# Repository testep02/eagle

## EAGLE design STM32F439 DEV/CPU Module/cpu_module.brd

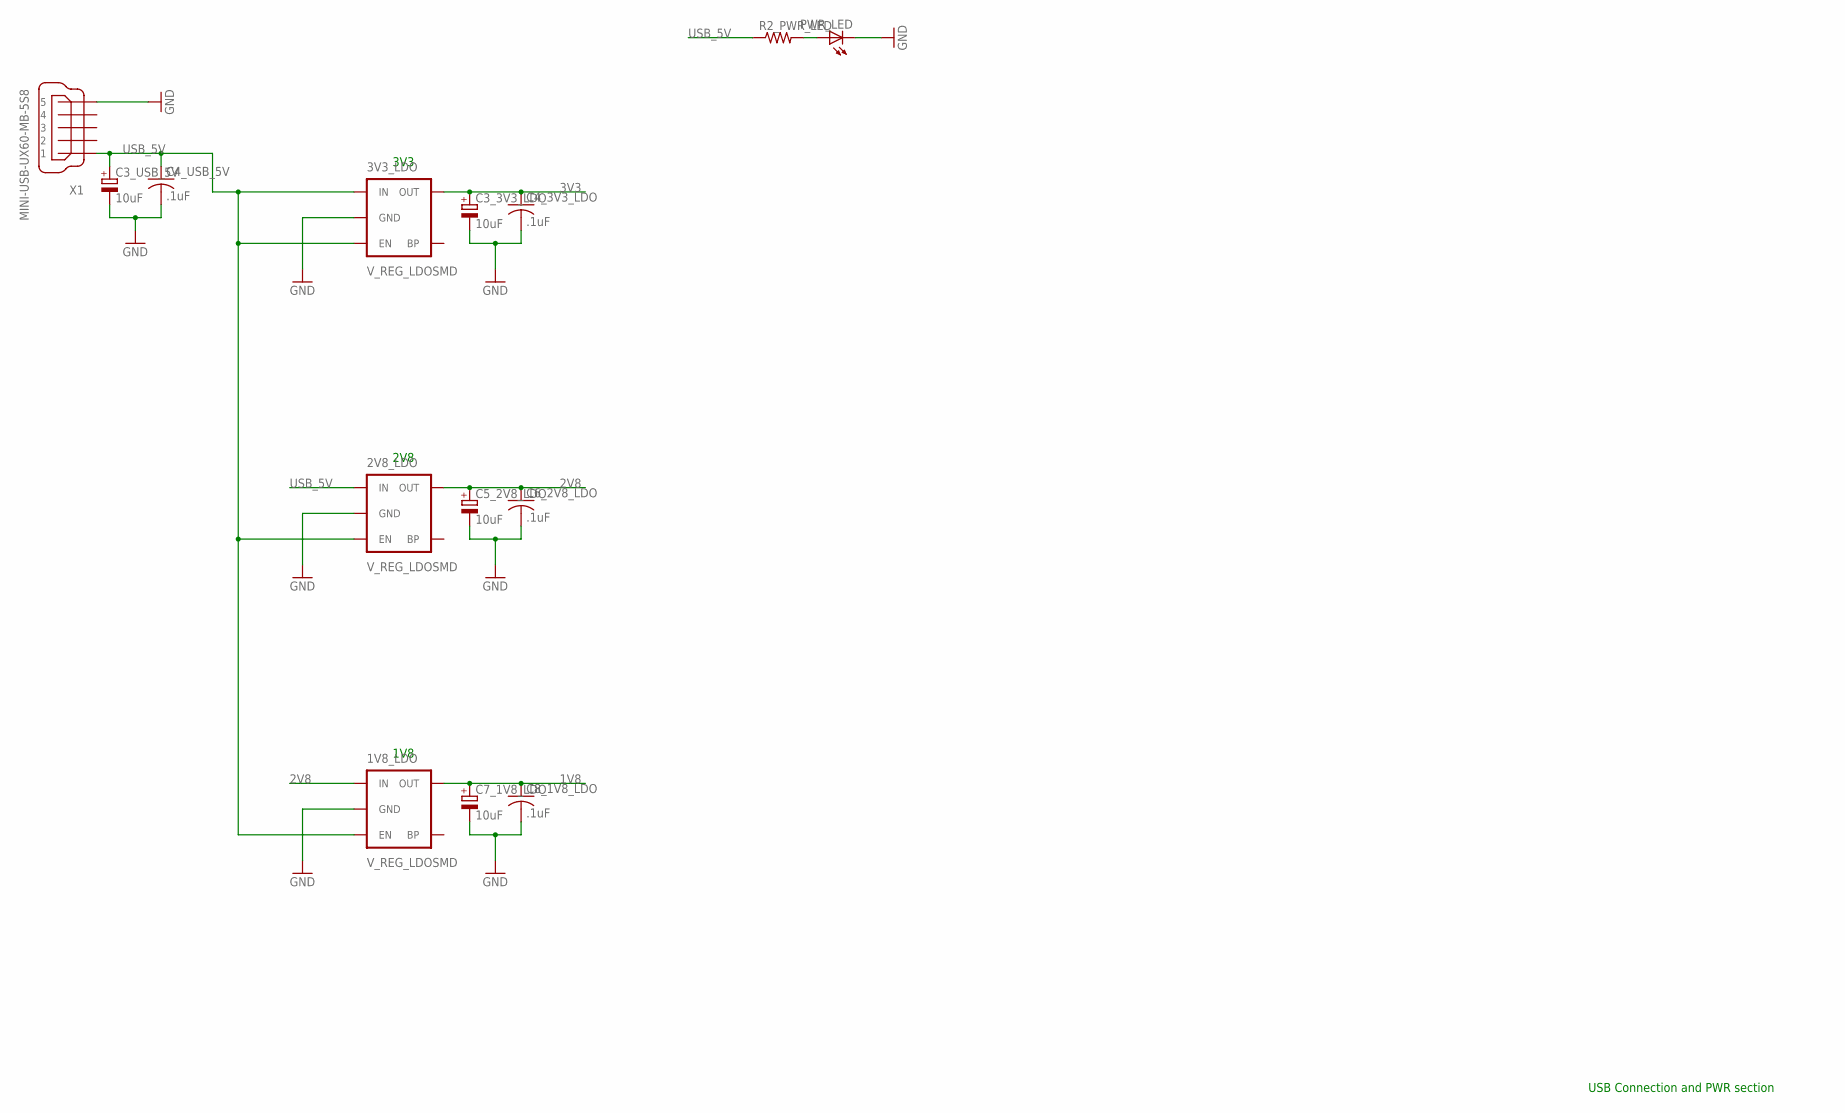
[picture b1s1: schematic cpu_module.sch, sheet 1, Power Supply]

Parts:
1V8_LDO, 2V8_LDO, 3V3_LDO: V_REG_LDOSMD; SOT23-5
C3_3V3_LDO, C3_USB_5V, C5_2V8_LDO, C7_1V8_LDO: 10uF; SMC_A
C4_3V3_LDO, C4_USB_5V, C6_2V8_LDO, C8_1V8_LDO: .1uF; C0402
PWR_LED: LEDCHIP-LED0603; CHIP-LED0603
R2_PWR_LED: RESISTOR0402-RES; 0402-RES
X1: MINI-USB-UX60-MB-5S8; UX60-MB-5S8

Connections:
1V8: 1V8_LDO.5 (OUT), C7_1V8_LDO.+, C8_1V8_LDO.1; also elsewhere on the board
2V8: 1V8_LDO.1 (IN), 2V8_LDO.5 (OUT), C5_2V8_LDO.+, C6_2V8_LDO.1; also elsewhere on the board
3V3: 3V3_LDO.5 (OUT), C3_3V3_LDO.+, C4_3V3_LDO.1; also elsewhere on the board
GND: 1V8_LDO.2 (GND), 2V8_LDO.2 (GND), 3V3_LDO.2 (GND), C3_3V3_LDO.-, C3_USB_5V.-, C4_3V3_LDO.2, C4_USB_5V.2, C5_2V8_LDO.-, C6_2V8_LDO.2, C7_1V8_LDO.-, C8_1V8_LDO.2, PWR_LED.C, X1.5; also elsewhere on the board
unnamed: PWR_LED.A, R2_PWR_LED.2
USB_5V: 1V8_LDO.3 (EN), 2V8_LDO.1 (IN), 2V8_LDO.3 (EN), 3V3_LDO.1 (IN), 3V3_LDO.3 (EN), C3_USB_5V.+, C4_USB_5V.1, R2_PWR_LED.1, X1.1; also elsewhere on the board

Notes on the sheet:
USB Connection and PWR section
3V3
2V8
1V8

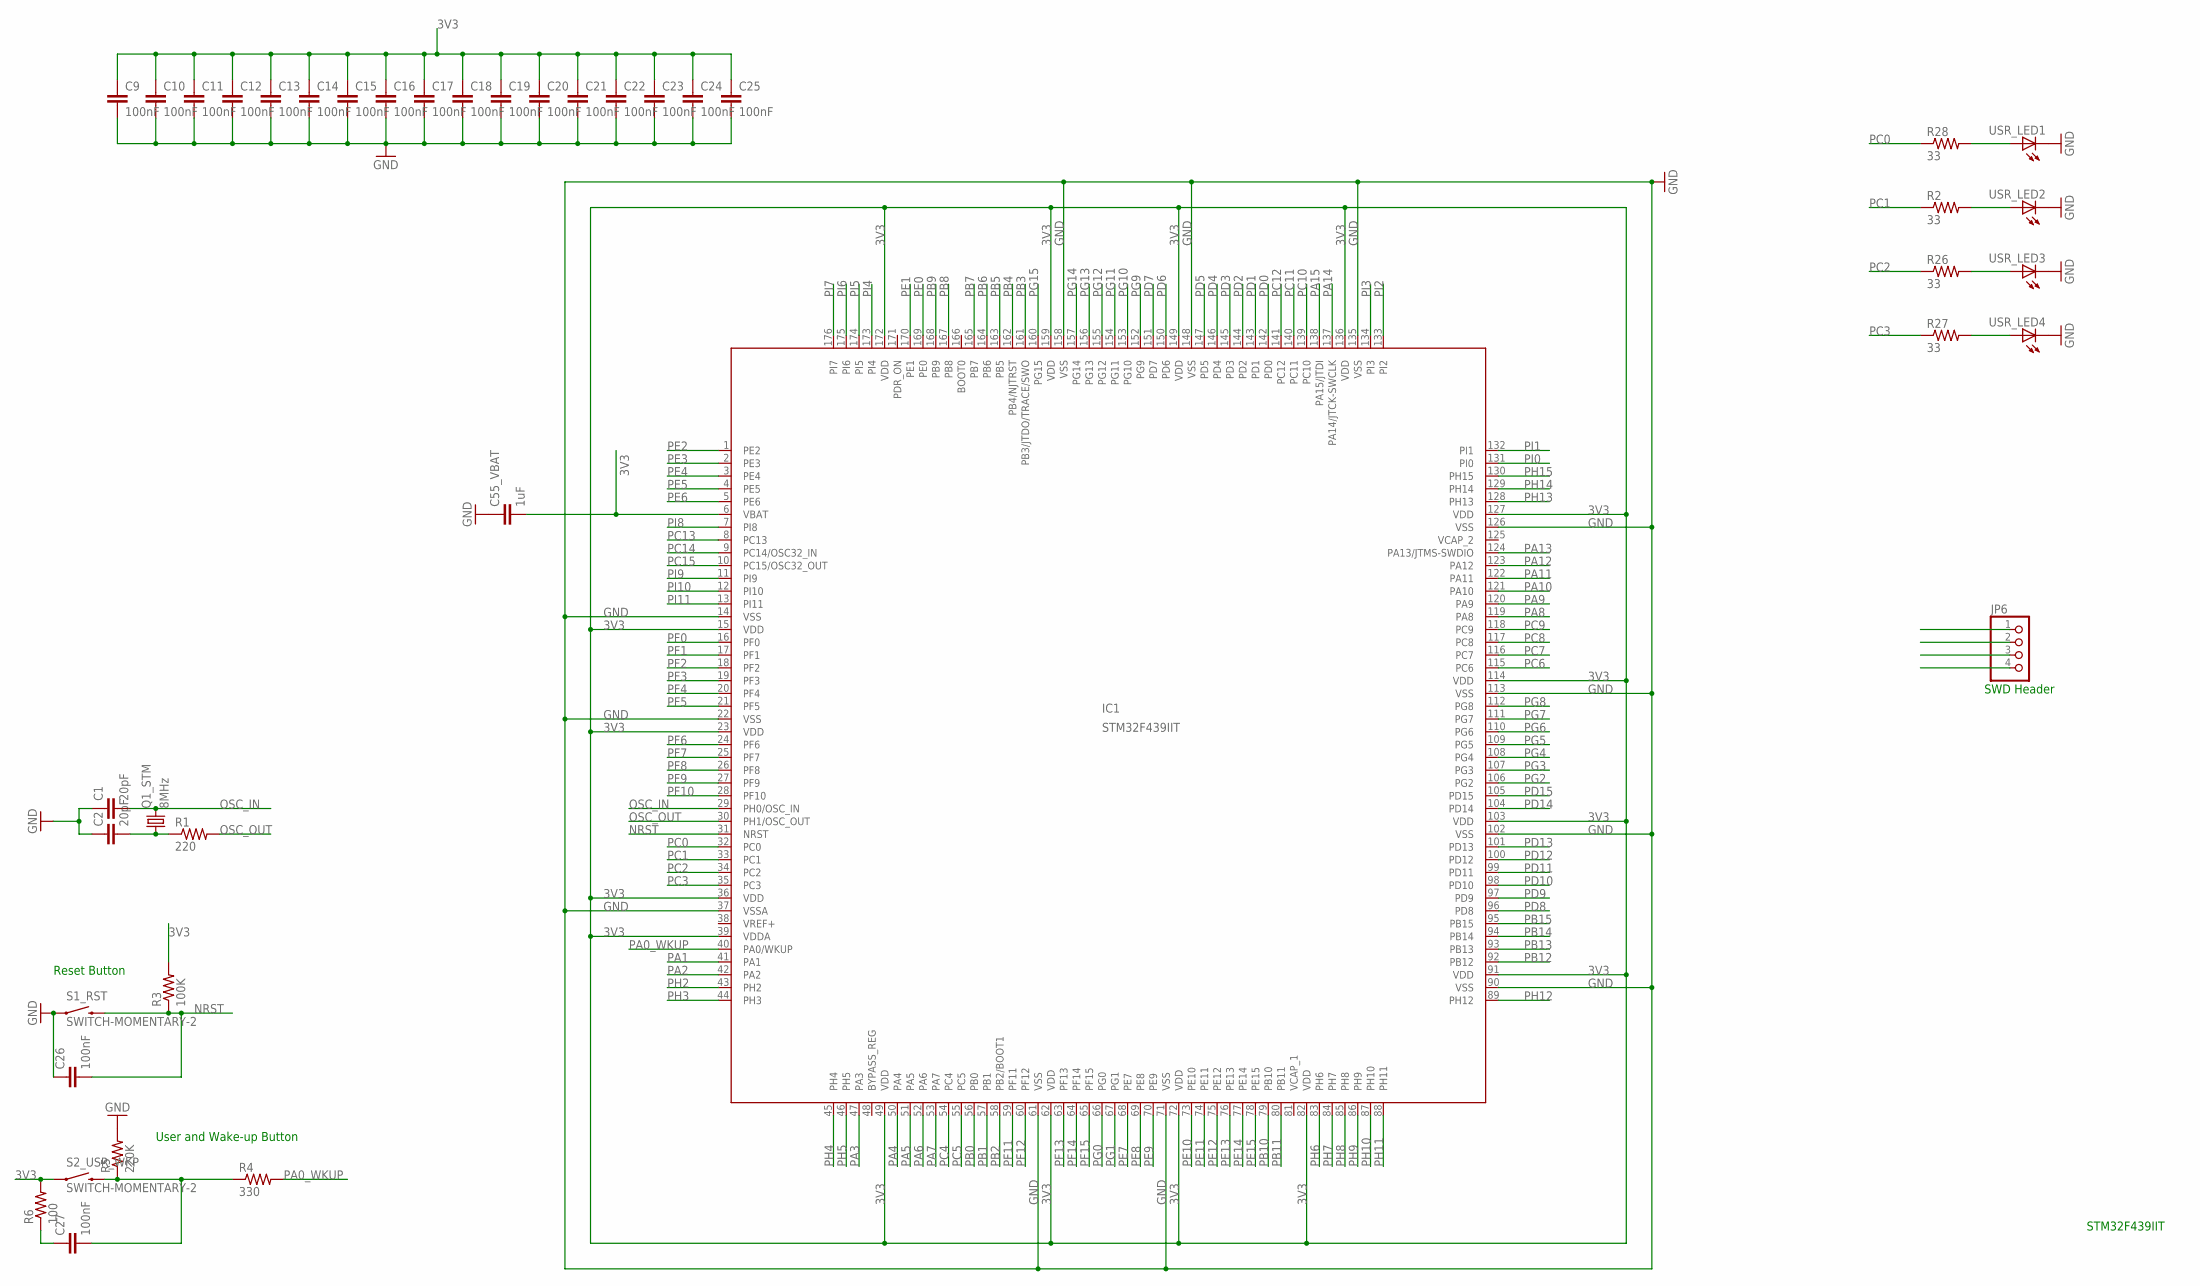
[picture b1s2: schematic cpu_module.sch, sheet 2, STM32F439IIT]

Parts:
C1, C2: 20pF; C0402
C9, C10, C11, C12, C13, C14, C15, C16, C17, C18, C19, C20, C21, C22, C23, C24, C25, C26, C27: 100nF; C0402
C55_VBAT: 1uF; C0402
IC1: STM32F439IIT; LQFP-176
JP6: PINHD-1X4/90; 1X04/90
Q1_STM: 8MHz; CTS406
R1: 220; 0402-RES
R2, R26, R27, R28: 33; 0402-RES
R3: 100K; 0402-RES
R4: 330; 0402-RES
R5: 220K; 0402-RES
R6: 100; 0402-RES
S1_RST, S2_USR_WKP: SWITCH-MOMENTARY-2; TACTILE_SWITCH_TALL
USR_LED1, USR_LED2, USR_LED3, USR_LED4: LEDCHIPLED_0805; CHIPLED_0805

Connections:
3V3: C9.1, C10.1, C11.1, C12.1, C13.1, C14.1, C15.1, C16.1, C17.1, C18.1, C19.1, C20.1, C21.1, C22.1, C23.1, C24.1, C25.1, C55_VBAT.2, IC1.6 (VBAT), IC1.15 (VDD), IC1.23 (VDD), IC1.36 (VDD), IC1.39 (VDDA), IC1.49 (VDD), IC1.62 (VDD), IC1.72 (VDD), IC1.82 (VDD), IC1.91 (VDD), IC1.103 (VDD), IC1.114 (VDD), IC1.127 (VDD), IC1.136 (VDD), IC1.149 (VDD), IC1.159 (VDD), IC1.172 (VDD), R3.2, R6.2, S2_USR_WKP.A2 (1); also elsewhere on the board
GND: C1.1, C2.1, C9.2, C10.2, C11.2, C12.2, C13.2, C14.2, C15.2, C16.2, C17.2, C18.2, C19.2, C20.2, C21.2, C22.2, C23.2, C24.2, C25.2, C26.1, C55_VBAT.1, IC1.14 (VSS), IC1.22 (VSS), IC1.37 (VSSA), IC1.61 (VSS), IC1.71 (VSS), IC1.90 (VSS), IC1.102 (VSS), IC1.113 (VSS), IC1.126 (VSS), IC1.135 (VSS), IC1.148 (VSS), IC1.158 (VSS), R5.2, S1_RST.A2 (1), USR_LED1.C, USR_LED2.C, USR_LED3.C, USR_LED4.C; also elsewhere on the board
unnamed: C2.2, Q1_STM.1, R1.1
unnamed: C27.2, R4.1, R5.1, S2_USR_WKP.B2 (2)
unnamed: C27.1, R6.1
unnamed: R28.2, USR_LED1.A
unnamed: R2.2, USR_LED2.A
unnamed: R26.2, USR_LED3.A
unnamed: R27.2, USR_LED4.A
NRST: C26.2, IC1.31 (NRST), R3.1, S1_RST.B2 (2); also elsewhere on the board
OSC_IN: C1.2, IC1.29 (PH0/OSC_IN), Q1_STM.3 (2)
OSC_OUT: IC1.30 (PH1/OSC_OUT), R1.2
PA0_WKUP: IC1.40 (PA0/WKUP), R4.2
PA1: IC1.41 (PA1); also elsewhere on the board
PA2: IC1.42 (PA2); also elsewhere on the board
PA3: IC1.47 (PA3); also elsewhere on the board
PA4: IC1.50 (PA4); also elsewhere on the board
PA5: IC1.51 (PA5); also elsewhere on the board
PA6: IC1.52 (PA6); also elsewhere on the board
PA7: IC1.53 (PA7); also elsewhere on the board
PA8: IC1.119 (PA8); also elsewhere on the board
PA9: IC1.120 (PA9); also elsewhere on the board
PA10: IC1.121 (PA10); also elsewhere on the board
PA11: IC1.122 (PA11); also elsewhere on the board
PA12: IC1.123 (PA12); also elsewhere on the board
PA13: IC1.124 (PA13/JTMS-SWDIO); also elsewhere on the board
PA14: IC1.137 (PA14/JTCK-SWCLK); also elsewhere on the board
PA15: IC1.138 (PA15/JTDI); also elsewhere on the board
PB0: IC1.56 (PB0); also elsewhere on the board
PB1: IC1.57 (PB1); also elsewhere on the board
PB2: IC1.58 (PB2/BOOT1); also elsewhere on the board
PB3: IC1.161 (PB3/JTDO/TRACE/SWO); also elsewhere on the board
PB4: IC1.162 (PB4/NJTRST); also elsewhere on the board
PB5: IC1.163 (PB5); also elsewhere on the board
PB6: IC1.164 (PB6); also elsewhere on the board
PB7: IC1.165 (PB7); also elsewhere on the board
PB8: IC1.167 (PB8); also elsewhere on the board
PB9: IC1.168 (PB9); also elsewhere on the board
PB10: IC1.79 (PB10); also elsewhere on the board
PB11: IC1.80 (PB11); also elsewhere on the board
PB12: IC1.92 (PB12); also elsewhere on the board
PB13: IC1.93 (PB13); also elsewhere on the board
PB14: IC1.94 (PB14); also elsewhere on the board
PB15: IC1.95 (PB15); also elsewhere on the board
PC0: IC1.32 (PC0), R28.1; also elsewhere on the board
PC1: IC1.33 (PC1), R2.1; also elsewhere on the board
PC2: IC1.34 (PC2), R26.1; also elsewhere on the board
PC3: IC1.35 (PC3), R27.1; also elsewhere on the board
PC4: IC1.54 (PC4); also elsewhere on the board
PC5: IC1.55 (PC5); also elsewhere on the board
PC6: IC1.115 (PC6); also elsewhere on the board
PC7: IC1.116 (PC7); also elsewhere on the board
PC8: IC1.117 (PC8); also elsewhere on the board
PC9: IC1.118 (PC9); also elsewhere on the board
PC10: IC1.139 (PC10); also elsewhere on the board
PC11: IC1.140 (PC11); also elsewhere on the board
PC12: IC1.141 (PC12); also elsewhere on the board
PC13: IC1.8 (PC13); also elsewhere on the board
PC14: IC1.9 (PC14/OSC32_IN); also elsewhere on the board
PC15: IC1.10 (PC15/OSC32_OUT); also elsewhere on the board
PD0: IC1.142 (PD0); also elsewhere on the board
PD1: IC1.143 (PD1); also elsewhere on the board
PD2: IC1.144 (PD2); also elsewhere on the board
PD3: IC1.145 (PD3); also elsewhere on the board
PD4: IC1.146 (PD4); also elsewhere on the board
PD5: IC1.147 (PD5); also elsewhere on the board
PD6: IC1.150 (PD6); also elsewhere on the board
PD7: IC1.151 (PD7); also elsewhere on the board
PD8: IC1.96 (PD8); also elsewhere on the board
PD9: IC1.97 (PD9); also elsewhere on the board
PD10: IC1.98 (PD10); also elsewhere on the board
PD11: IC1.99 (PD11); also elsewhere on the board
PD12: IC1.100 (PD12); also elsewhere on the board
PD13: IC1.101 (PD13); also elsewhere on the board
PD14: IC1.104 (PD14); also elsewhere on the board
PD15: IC1.105 (PD15); also elsewhere on the board
PDR_ON: IC1.171 (PDR_ON)
PE0: IC1.169 (PE0); also elsewhere on the board
PE1: IC1.170 (PE1); also elsewhere on the board
PE2: IC1.1 (PE2); also elsewhere on the board
PE3: IC1.2 (PE3); also elsewhere on the board
PE4: IC1.3 (PE4); also elsewhere on the board
PE5: IC1.4 (PE5); also elsewhere on the board
PE6: IC1.5 (PE6); also elsewhere on the board
PE7: IC1.68 (PE7); also elsewhere on the board
PE8: IC1.69 (PE8); also elsewhere on the board
PE9: IC1.70 (PE9); also elsewhere on the board
PE10: IC1.73 (PE10); also elsewhere on the board
PE11: IC1.74 (PE11); also elsewhere on the board
PE12: IC1.75 (PE12); also elsewhere on the board
PE13: IC1.76 (PE13); also elsewhere on the board
PE14: IC1.77 (PE14); also elsewhere on the board
PE15: IC1.78 (PE15); also elsewhere on the board
PF0: IC1.16 (PF0); also elsewhere on the board
PF1: IC1.17 (PF1); also elsewhere on the board
PF2: IC1.18 (PF2); also elsewhere on the board
PF3: IC1.19 (PF3); also elsewhere on the board
PF4: IC1.20 (PF4); also elsewhere on the board
PF5: IC1.21 (PF5); also elsewhere on the board
PF6: IC1.24 (PF6); also elsewhere on the board
PF7: IC1.25 (PF7); also elsewhere on the board
PF8: IC1.26 (PF8); also elsewhere on the board
PF9: IC1.27 (PF9); also elsewhere on the board
PF10: IC1.28 (PF10); also elsewhere on the board
PF11: IC1.59 (PF11); also elsewhere on the board
PF12: IC1.60 (PF12); also elsewhere on the board
PF13: IC1.63 (PF13); also elsewhere on the board
PF14: IC1.64 (PF14); also elsewhere on the board
PF15: IC1.65 (PF15); also elsewhere on the board
PG0: IC1.66 (PG0); also elsewhere on the board
PG1: IC1.67 (PG1); also elsewhere on the board
PG2: IC1.106 (PG2); also elsewhere on the board
PG3: IC1.107 (PG3); also elsewhere on the board
PG4: IC1.108 (PG4); also elsewhere on the board
PG5: IC1.109 (PG5); also elsewhere on the board
PG6: IC1.110 (PG6); also elsewhere on the board
PG7: IC1.111 (PG7); also elsewhere on the board
PG8: IC1.112 (PG8); also elsewhere on the board
PG9: IC1.152 (PG9); also elsewhere on the board
PG10: IC1.153 (PG10); also elsewhere on the board
PG11: IC1.154 (PG11); also elsewhere on the board
PG12: IC1.155 (PG12); also elsewhere on the board
PG13: IC1.156 (PG13); also elsewhere on the board
PG14: IC1.157 (PG14); also elsewhere on the board
PG15: IC1.160 (PG15); also elsewhere on the board
PH2: IC1.43 (PH2); also elsewhere on the board
PH3: IC1.44 (PH3); also elsewhere on the board
PH4: IC1.45 (PH4); also elsewhere on the board
PH5: IC1.46 (PH5); also elsewhere on the board
PH6: IC1.83 (PH6); also elsewhere on the board
PH7: IC1.84 (PH7); also elsewhere on the board
PH8: IC1.85 (PH8); also elsewhere on the board
PH9: IC1.86 (PH9); also elsewhere on the board
PH10: IC1.87 (PH10); also elsewhere on the board
PH11: IC1.88 (PH11); also elsewhere on the board
PH12: IC1.89 (PH12); also elsewhere on the board
PH13: IC1.128 (PH13); also elsewhere on the board
PH14: IC1.129 (PH14); also elsewhere on the board
PH15: IC1.130 (PH15); also elsewhere on the board
PI0: IC1.131 (PI0); also elsewhere on the board
PI1: IC1.132 (PI1); also elsewhere on the board
PI2: IC1.133 (PI2); also elsewhere on the board
PI3: IC1.134 (PI3); also elsewhere on the board
PI4: IC1.173 (PI4); also elsewhere on the board
PI5: IC1.174 (PI5); also elsewhere on the board
PI6: IC1.175 (PI6); also elsewhere on the board
PI7: IC1.176 (PI7); also elsewhere on the board
PI8: IC1.7 (PI8); also elsewhere on the board
PI9: IC1.11 (PI9); also elsewhere on the board
PI10: IC1.12 (PI10); also elsewhere on the board
PI11: IC1.13 (PI11); also elsewhere on the board
VCAP_1: IC1.81 (VCAP_1)
VCAP_2: IC1.125 (VCAP_2)
VREF+: IC1.38 (VREF+)

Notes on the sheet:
STM32F439IIT
Reset Button
User and Wake-up Button
SWD Header

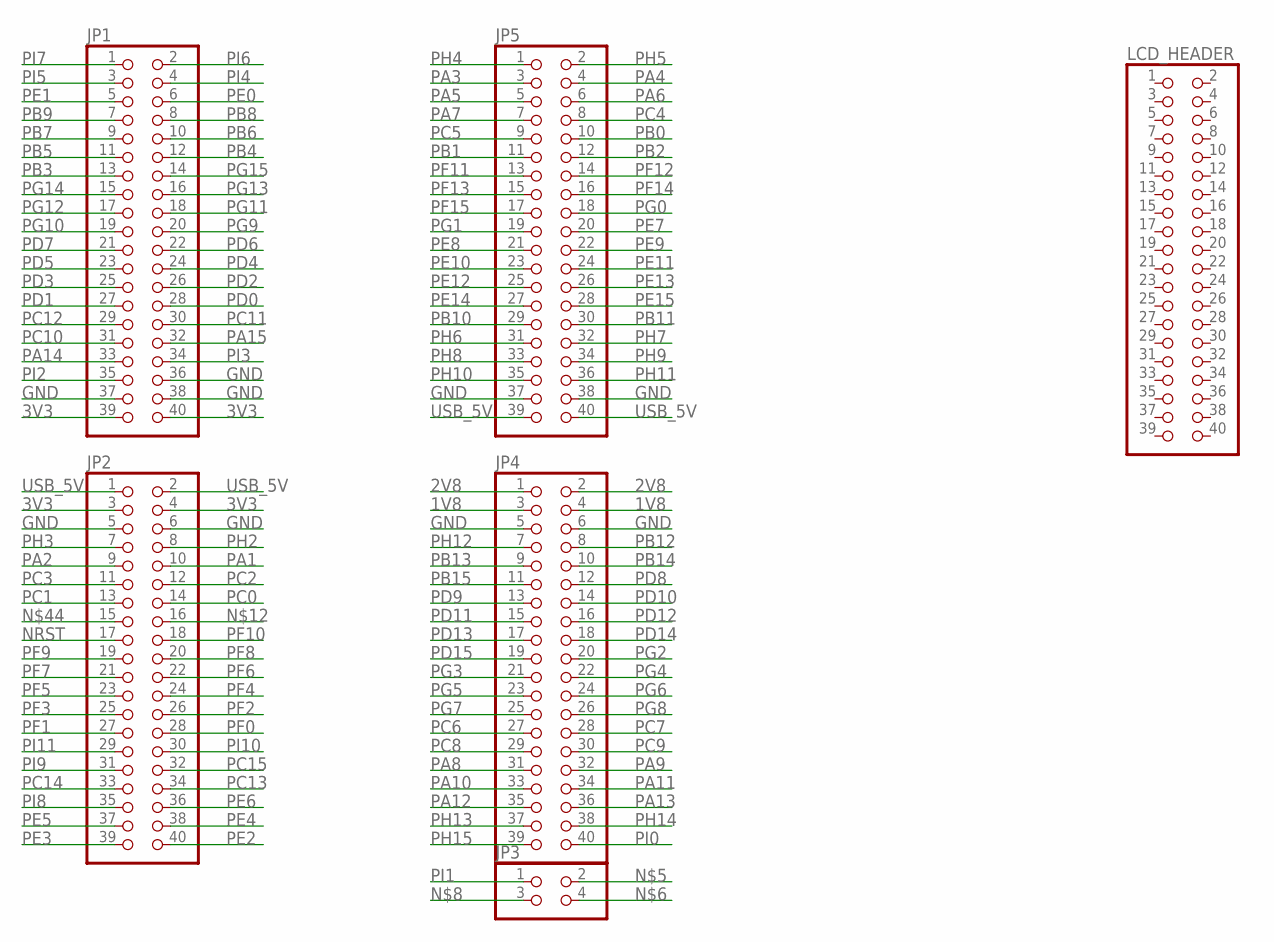
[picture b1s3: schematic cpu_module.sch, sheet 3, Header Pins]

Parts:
JP1, JP2, JP4, JP5: PINHD-2X20; 2X20
JP3: PINHD-2X2; 2X02
LCD_HEADER: PINHD-2X20; 2X20

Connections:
1V8: JP4.3, JP4.4; also elsewhere on the board
2V8: JP4.1, JP4.2; also elsewhere on the board
3V3: JP1.39, JP1.40, JP2.3, JP2.4; also elsewhere on the board
GND: JP1.36, JP1.37, JP1.38, JP2.5, JP2.6, JP4.5, JP4.6, JP5.37, JP5.38; also elsewhere on the board
NRST: JP2.17; also elsewhere on the board
PA1: JP2.10; also elsewhere on the board
PA2: JP2.9; also elsewhere on the board
PA3: JP5.3; also elsewhere on the board
PA4: JP5.4; also elsewhere on the board
PA5: JP5.5; also elsewhere on the board
PA6: JP5.6; also elsewhere on the board
PA7: JP5.7; also elsewhere on the board
PA8: JP4.31; also elsewhere on the board
PA9: JP4.32; also elsewhere on the board
PA10: JP4.33; also elsewhere on the board
PA11: JP4.34; also elsewhere on the board
PA12: JP4.35; also elsewhere on the board
PA13: JP4.36; also elsewhere on the board
PA14: JP1.33; also elsewhere on the board
PA15: JP1.32; also elsewhere on the board
PB0: JP5.10; also elsewhere on the board
PB1: JP5.11; also elsewhere on the board
PB2: JP5.12; also elsewhere on the board
PB3: JP1.13; also elsewhere on the board
PB4: JP1.12; also elsewhere on the board
PB5: JP1.11; also elsewhere on the board
PB6: JP1.10; also elsewhere on the board
PB7: JP1.9; also elsewhere on the board
PB8: JP1.8; also elsewhere on the board
PB9: JP1.7; also elsewhere on the board
PB10: JP5.29; also elsewhere on the board
PB11: JP5.30; also elsewhere on the board
PB12: JP4.8; also elsewhere on the board
PB13: JP4.9; also elsewhere on the board
PB14: JP4.10; also elsewhere on the board
PB15: JP4.11; also elsewhere on the board
PC0: JP2.14; also elsewhere on the board
PC1: JP2.13; also elsewhere on the board
PC2: JP2.12; also elsewhere on the board
PC3: JP2.11; also elsewhere on the board
PC4: JP5.8; also elsewhere on the board
PC5: JP5.9; also elsewhere on the board
PC6: JP4.27; also elsewhere on the board
PC7: JP4.28; also elsewhere on the board
PC8: JP4.29; also elsewhere on the board
PC9: JP4.30; also elsewhere on the board
PC10: JP1.31; also elsewhere on the board
PC11: JP1.30; also elsewhere on the board
PC12: JP1.29; also elsewhere on the board
PC13: JP2.34; also elsewhere on the board
PC14: JP2.33; also elsewhere on the board
PC15: JP2.32; also elsewhere on the board
PD0: JP1.28; also elsewhere on the board
PD1: JP1.27; also elsewhere on the board
PD2: JP1.26; also elsewhere on the board
PD3: JP1.25; also elsewhere on the board
PD4: JP1.24; also elsewhere on the board
PD5: JP1.23; also elsewhere on the board
PD6: JP1.22; also elsewhere on the board
PD7: JP1.21; also elsewhere on the board
PD8: JP4.12; also elsewhere on the board
PD9: JP4.13; also elsewhere on the board
PD10: JP4.14; also elsewhere on the board
PD11: JP4.15; also elsewhere on the board
PD12: JP4.16; also elsewhere on the board
PD13: JP4.17; also elsewhere on the board
PD14: JP4.18; also elsewhere on the board
PD15: JP4.19; also elsewhere on the board
PE0: JP1.6; also elsewhere on the board
PE1: JP1.5; also elsewhere on the board
PE2: JP2.40; also elsewhere on the board
PE3: JP2.39; also elsewhere on the board
PE4: JP2.38; also elsewhere on the board
PE5: JP2.37; also elsewhere on the board
PE6: JP2.36; also elsewhere on the board
PE7: JP5.20; also elsewhere on the board
PE8: JP5.21; also elsewhere on the board
PE9: JP5.22; also elsewhere on the board
PE10: JP5.23; also elsewhere on the board
PE11: JP5.24; also elsewhere on the board
PE12: JP5.25; also elsewhere on the board
PE13: JP5.26; also elsewhere on the board
PE14: JP5.27; also elsewhere on the board
PE15: JP5.28; also elsewhere on the board
PF0: JP2.28; also elsewhere on the board
PF1: JP2.27; also elsewhere on the board
PF2: JP2.26; also elsewhere on the board
PF3: JP2.25; also elsewhere on the board
PF4: JP2.24; also elsewhere on the board
PF5: JP2.23; also elsewhere on the board
PF6: JP2.22; also elsewhere on the board
PF7: JP2.21; also elsewhere on the board
PF8: JP2.20; also elsewhere on the board
PF9: JP2.19; also elsewhere on the board
PF10: JP2.18; also elsewhere on the board
PF11: JP5.13; also elsewhere on the board
PF12: JP5.14; also elsewhere on the board
PF13: JP5.15; also elsewhere on the board
PF14: JP5.16; also elsewhere on the board
PF15: JP5.17; also elsewhere on the board
PG0: JP5.18; also elsewhere on the board
PG1: JP5.19; also elsewhere on the board
PG2: JP4.20; also elsewhere on the board
PG3: JP4.21; also elsewhere on the board
PG4: JP4.22; also elsewhere on the board
PG5: JP4.23; also elsewhere on the board
PG6: JP4.24; also elsewhere on the board
PG7: JP4.25; also elsewhere on the board
PG8: JP4.26; also elsewhere on the board
PG9: JP1.20; also elsewhere on the board
PG10: JP1.19; also elsewhere on the board
PG11: JP1.18; also elsewhere on the board
PG12: JP1.17; also elsewhere on the board
PG13: JP1.16; also elsewhere on the board
PG14: JP1.15; also elsewhere on the board
PG15: JP1.14; also elsewhere on the board
PH2: JP2.8; also elsewhere on the board
PH3: JP2.7; also elsewhere on the board
PH4: JP5.1; also elsewhere on the board
PH5: JP5.2; also elsewhere on the board
PH6: JP5.31; also elsewhere on the board
PH7: JP5.32; also elsewhere on the board
PH8: JP5.33; also elsewhere on the board
PH9: JP5.34; also elsewhere on the board
PH10: JP5.35; also elsewhere on the board
PH11: JP5.36; also elsewhere on the board
PH12: JP4.7; also elsewhere on the board
PH13: JP4.37; also elsewhere on the board
PH14: JP4.38; also elsewhere on the board
PH15: JP4.39; also elsewhere on the board
PI0: JP4.40; also elsewhere on the board
PI1: JP3.1; also elsewhere on the board
PI2: JP1.35; also elsewhere on the board
PI3: JP1.34; also elsewhere on the board
PI4: JP1.4; also elsewhere on the board
PI5: JP1.3; also elsewhere on the board
PI6: JP1.2; also elsewhere on the board
PI7: JP1.1; also elsewhere on the board
PI8: JP2.35; also elsewhere on the board
PI9: JP2.31; also elsewhere on the board
PI10: JP2.30; also elsewhere on the board
PI11: JP2.29; also elsewhere on the board
USB_5V: JP2.1, JP2.2, JP5.39, JP5.40; also elsewhere on the board

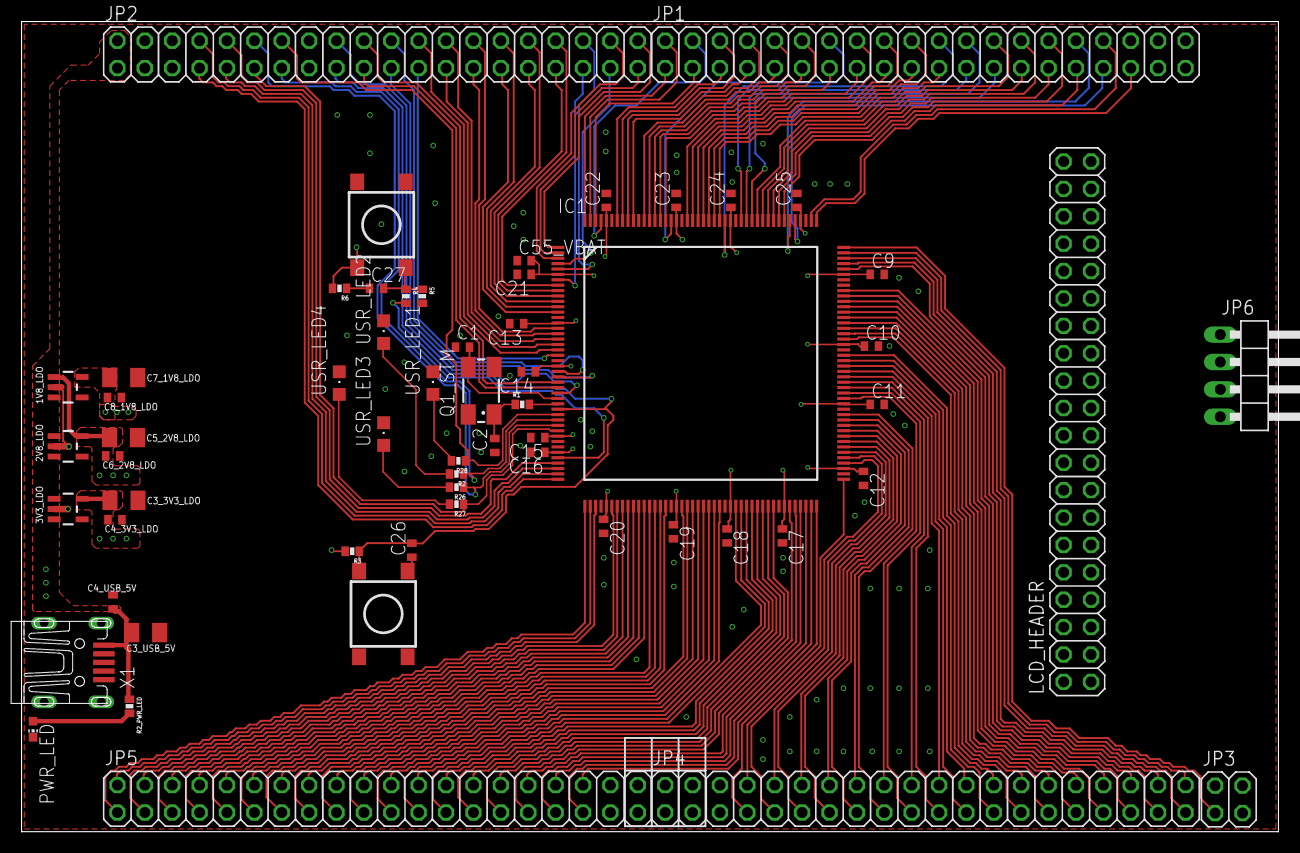
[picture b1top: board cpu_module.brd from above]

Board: 4 copper layers, 116.6 x 75.1 mm, 60 parts (0 on the bottom side), 154 nets.

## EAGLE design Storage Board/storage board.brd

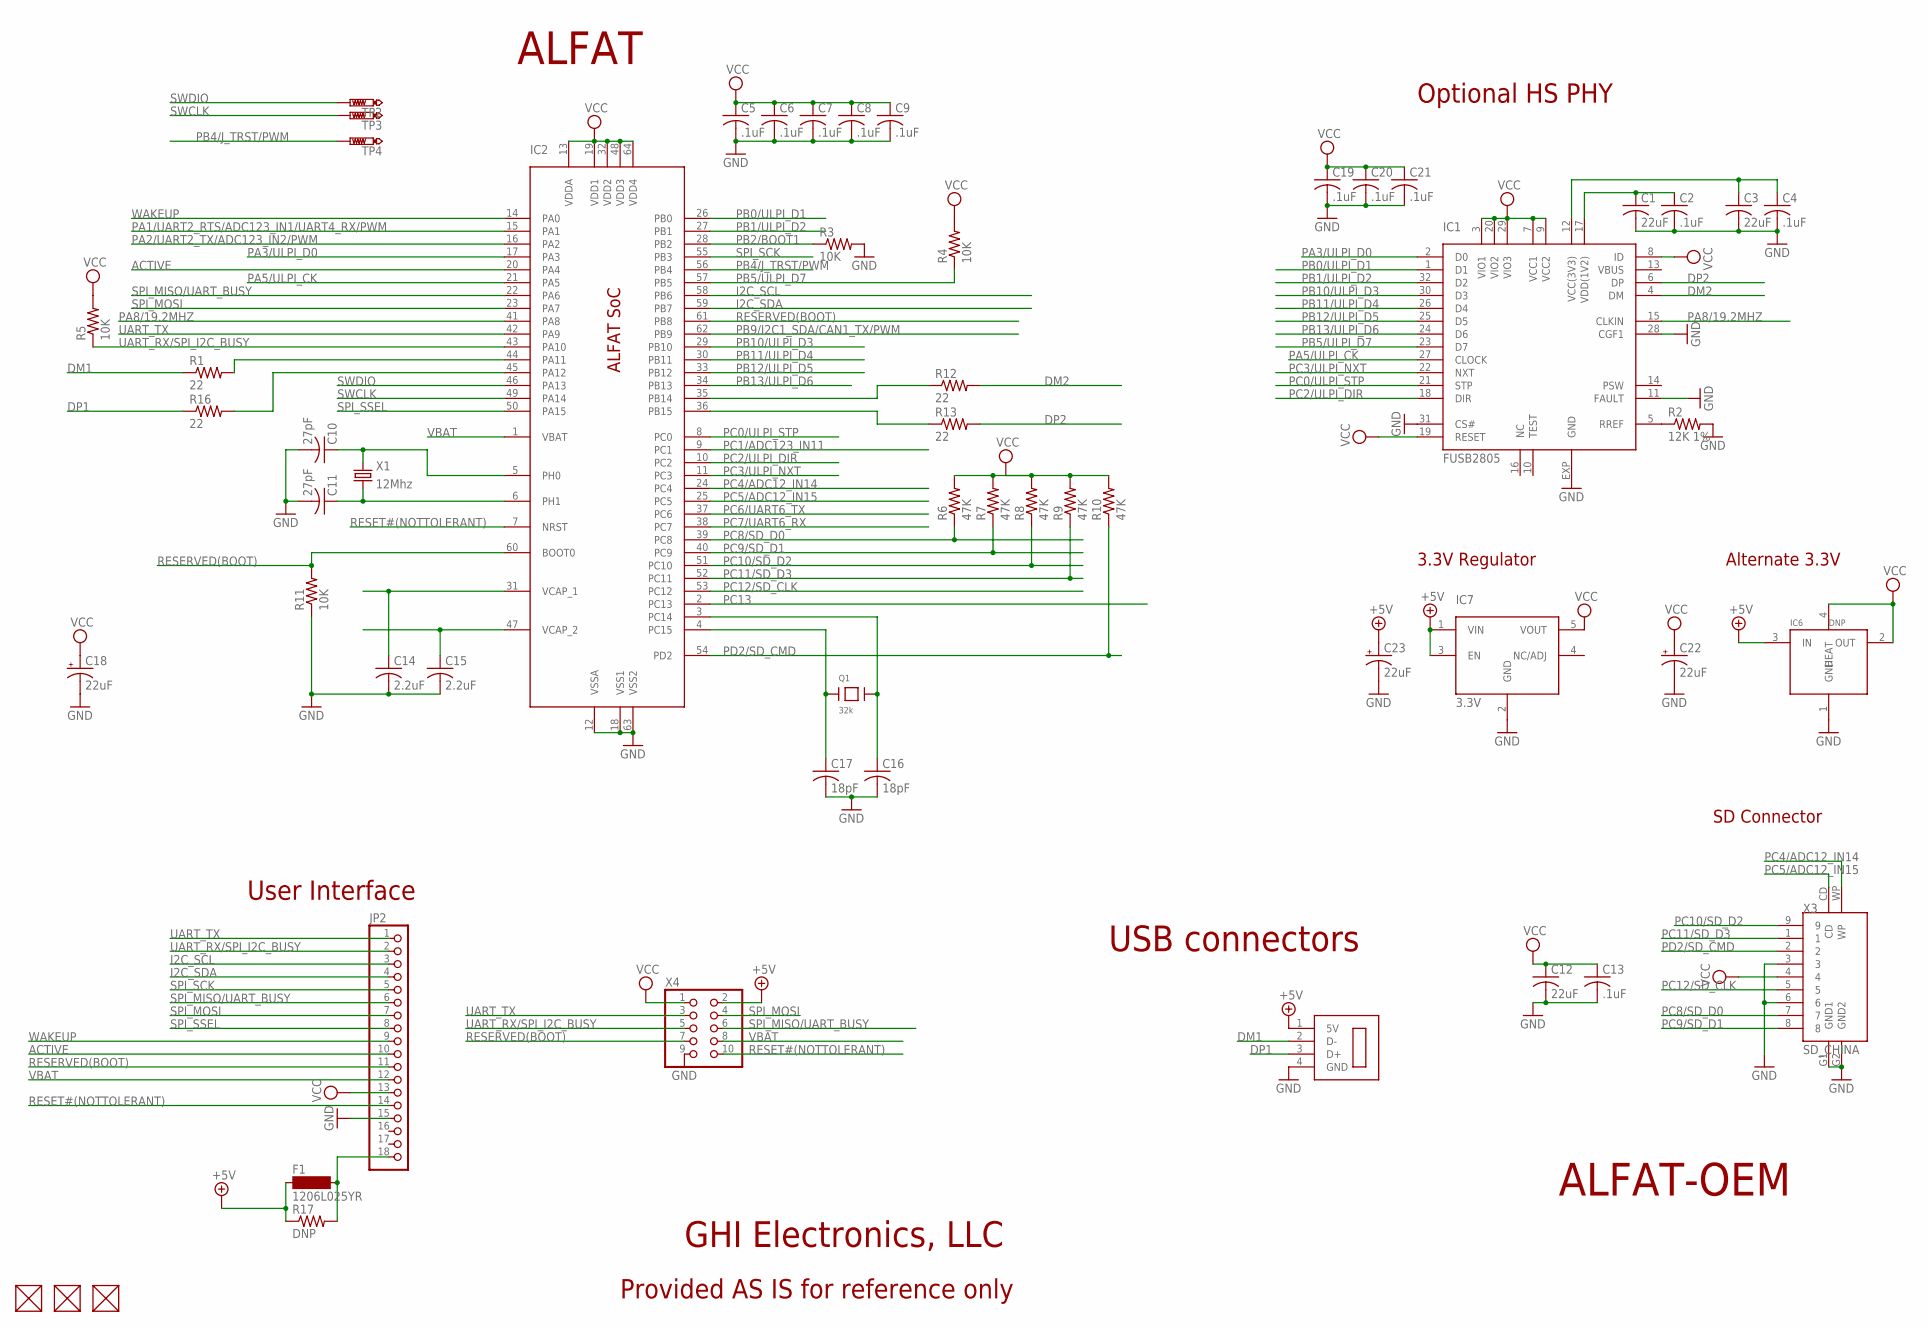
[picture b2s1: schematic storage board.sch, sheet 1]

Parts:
C1, C3, C12: 22uF; C0805K
C2, C4, C5, C6, C7, C8, C9, C13, C19, C20, C21: .1uF; C0603K
C10, C11: 27pF; C0603K
C14, C15: 2.2uF; C0805K
C16, C17: 18pF; C0603K
C18, C22, C23: 22uF; CT3528
F1: 1206L025YR; SM-1206
FUD1, FUD2, FUD3: FIDUCIAL; FIDUCIAL_40MIL
IC1: FUSB2805; MLP32
IC2: STM32F40X; LQFP64
IC6: DNP; SOT89
IC7: 3.3V; SOT23-5
JP2: PINHD-1X18; 1X18
Q1: 32k; CRYSTAL_3.2X1.5
R1, R12, R13, R16: 22; R0603
R2: 12K 1%; R0603
R3, R4, R5, R11: 10K; R0603
R6, R7, R8, R9, R10: 47K; R0603
R17: DNP; R0603
TP2, TP3, TP4: PTR1B1,27; B1,27
X1: 12Mhz; SM49@1
X2: USB_HOST_CON
X3: SD_CHINA
X4: PINHD-2X5; 2X05

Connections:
+5V: C23.+, F1.1, IC6.3 (IN), IC7.1 (VIN), IC7.3 (EN), R17.1, X2.1 (5V), X4.2
ACTIVE: IC2.20 (PA4), JP2.10
DM1: R1.1, X2.2 (D-)
DM2: IC1.4 (DM), R12.2
DP1: R16.1, X2.3 (D+)
DP2: IC1.6 (DP), R13.2
GND: C1.2, C2.2, C3.2, C4.2, C5.2, C6.2, C7.2, C8.2, C9.2, C10.2, C11.2, C12.2, C13.2, C14.2, C15.2, C16.2, C17.2, C18.-, C19.2, C20.2, C21.2, C22.-, C23.-, IC1.11 (FAULT), IC1.28 (CGF1), IC1.31 (CS#), IC1.EXP (GND), IC2.12 (VSSA), IC2.18 (VSS1), IC2.63 (VSS2), IC6.1 (GND), IC7.2 (GND), JP2.15, R2.2, R3.2, R11.1, X2.4 (GND), X2.8 (GND), X3.3, X3.6, X3.G1 (GND1), X3.G2 (GND2), X4.9
I2C_SCL: IC2.58 (PB6), JP2.3
I2C_SDA: IC2.59 (PB7), JP2.4
unnamed: C15.1, IC2.47 (VCAP_2)
unnamed: C14.1, IC2.31 (VCAP_1)
unnamed: IC1.5 (RREF), R2.1
unnamed: IC2.44 (PA11), R1.2
unnamed: C1.1, C2.1, IC1.17 (VDD(1V2))
unnamed: C3.1, C4.1, IC1.12 (VCC(3V3))
unnamed: IC2.45 (PA12), R16.2
unnamed: IC2.35 (PB14), R12.1
unnamed: IC2.36 (PB15), R13.1
unnamed: F1.2, JP2.18, R17.2
PA1/UART2_RTS/ADC123_IN1/UART4_RX/PWM: IC2.15 (PA1)
PA2/UART2_TX/ADC123_IN2/PWM: IC2.16 (PA2)
PA3/ULPI_D0: IC1.2 (D0), IC2.17 (PA3)
PA5/ULPI_CK: IC1.27 (CLOCK), IC2.21 (PA5)
PA8/19.2MHZ: IC1.15 (CLKIN), IC2.41 (PA8)
PB0/ULPI_D1: IC1.1 (D1), IC2.26 (PB0)
PB1/ULPI_D2: IC1.32 (D2), IC2.27 (PB1)
PB2/BOOT1: IC2.28 (PB2), R3.1
PB4/J_TRST/PWM: IC2.56 (PB4), TP4.PP
PB5/ULPI_D7: IC1.23 (D7), IC2.57 (PB5), R4.1
PB9/I2C1_SDA/CAN1_TX/PWM: IC2.62 (PB9)
PB10/ULPI_D3: IC1.30 (D3), IC2.29 (PB10)
PB11/ULPI_D4: IC1.26 (D4), IC2.30 (PB11)
PB12/ULPI_D5: IC1.25 (D5), IC2.33 (PB12)
PB13/ULPI_D6: IC1.24 (D6), IC2.34 (PB13)
PC0/ULPI_STP: IC1.21 (STP), IC2.8 (PC0)
PC1/ADC123_IN11: IC2.9 (PC1)
PC2/ULPI_DIR: IC1.18 (DIR), IC2.10 (PC2)
PC3/ULPI_NXT: IC1.22 (NXT), IC2.11 (PC3)
PC4/ADC12_IN14: IC2.24 (PC4), X3.WP
PC5/ADC12_IN15: IC2.25 (PC5), X3.CD
PC6/UART6_TX: IC2.37 (PC6)
PC7/UART6_RX: IC2.38 (PC7)
PC8/SD_D0: IC2.39 (PC8), R6.1, X3.7
PC9/SD_D1: IC2.40 (PC9), R7.1, X3.8
PC10/SD_D2: IC2.51 (PC10), R8.1, X3.9
PC11/SD_D3: IC2.52 (PC11), R9.1, X3.1
PC12/SD_CLK: IC2.53 (PC12), X3.5
PC13: IC2.2 (PC13)
PD2/SD_CMD: IC2.54 (PD2), R10.1, X3.2
RESERVED(BOOT): IC2.60 (BOOT0), IC2.61 (PB8), JP2.11, R11.2, X4.7
RESET#(NOTTOLERANT): IC2.7 (NRST), JP2.14, X4.10
SPI_MISO/UART_BUSY: IC2.22 (PA6), JP2.6, X4.6
SPI_MOSI: IC2.23 (PA7), JP2.7, X4.4
SPI_SCK: IC2.55 (PB3), JP2.5
SPI_SSEL: IC2.50 (PA15), JP2.8
SWCLK: IC2.49 (PA14), TP3.PP
SWDIO: IC2.46 (PA13), TP2.PP
UART_RX/SPI_I2C_BUSY: IC2.43 (PA10), JP2.2, R5.1, X4.5
UART_TX: IC2.42 (PA9), JP2.1, X4.3
VBAT: IC2.1 (VBAT), JP2.12, X4.8
VCC: C5.1, C6.1, C7.1, C8.1, C9.1, C12.1, C13.1, C18.+, C19.1, C20.1, C21.1, C22.+, IC1.3 (VIO1), IC1.7 (VCC1), IC1.8 (ID), IC1.9 (VCC2), IC1.19 (RESET), IC1.20 (VIO2), IC1.29 (VIO3), IC2.13 (VDDA), IC2.19 (VDD1), IC2.32 (VDD2), IC2.48 (VDD3), IC2.64 (VDD4), IC6.2 (OUT), IC6.4 (HEAT), IC7.5 (VOUT), JP2.13, R4.2, R5.2, R6.2, R7.2, R8.2, R9.2, R10.2, X3.4, X4.1
WAKEUP: IC2.14 (PA0), JP2.9
XI32: C17.1, IC2.4 (PC15), Q1.P$1
XO32: C16.1, IC2.3 (PC14), Q1.P$2
XTAL3: C10.1, IC2.5 (PH0), X1.2
XTAL4: C11.1, IC2.6 (PH1), X1.1

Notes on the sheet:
User Interface
USB connectors
3.3V Regulator
Alternate 3.3V
SD Connector
ALFAT SoC
ALFAT-OEM
Provided AS IS for reference only
Optional HS PHY
ALFAT
GHI Electronics, LLC

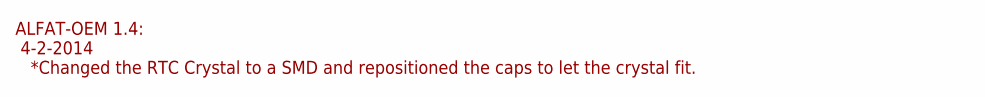
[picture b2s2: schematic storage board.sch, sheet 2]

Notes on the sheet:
ALFAT-OEM 1.4: 4-2-2014 *Changed the RTC Crystal to a SMD and repositioned the caps to let the crystal fit.

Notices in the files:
parts and their libraries:
SparkFun-Passives: Licensing: CC v3.0 Share-Alike You are welcome to use this library for commercial purposes.
